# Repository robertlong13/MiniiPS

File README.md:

# MiniiPS
Custom regulator board for miniaturized Wii. Provides 1V, 1.15V, 3.3V, 5V. Similar to the PowerMiiLite, but larger and a few extra features specific to my personal project. Should be good for any wall-powered mini Wii project.

### Goals for this power supply
* Be small. Can't really afford much more space than 20mm by 60mm
* Use a 5V 3A USB-C charger for input power
* Have an enable pin for turning on and off the power supply. The slide switch I'm using for power is only rated for 200mA.
* Design the 3.3V, 1.15V, and 1V regulators for 3A output, and 15V input voltage. I'm over-engineering to give myself maximum chance of getting it right on the first try, instead of pushing all my components right to their spec. There could be some reason I this is a bad idea, but I can't think of one.
* Be easy to hand assemble (using skillet reflow) and rework. An automated assembly run is out of the question. Smallest passives are 0603 (1608 metric).

To power on the outputs, the enable pad must be pulled high with your power switch. By default, that pad is pulled low with a 10K resistor.

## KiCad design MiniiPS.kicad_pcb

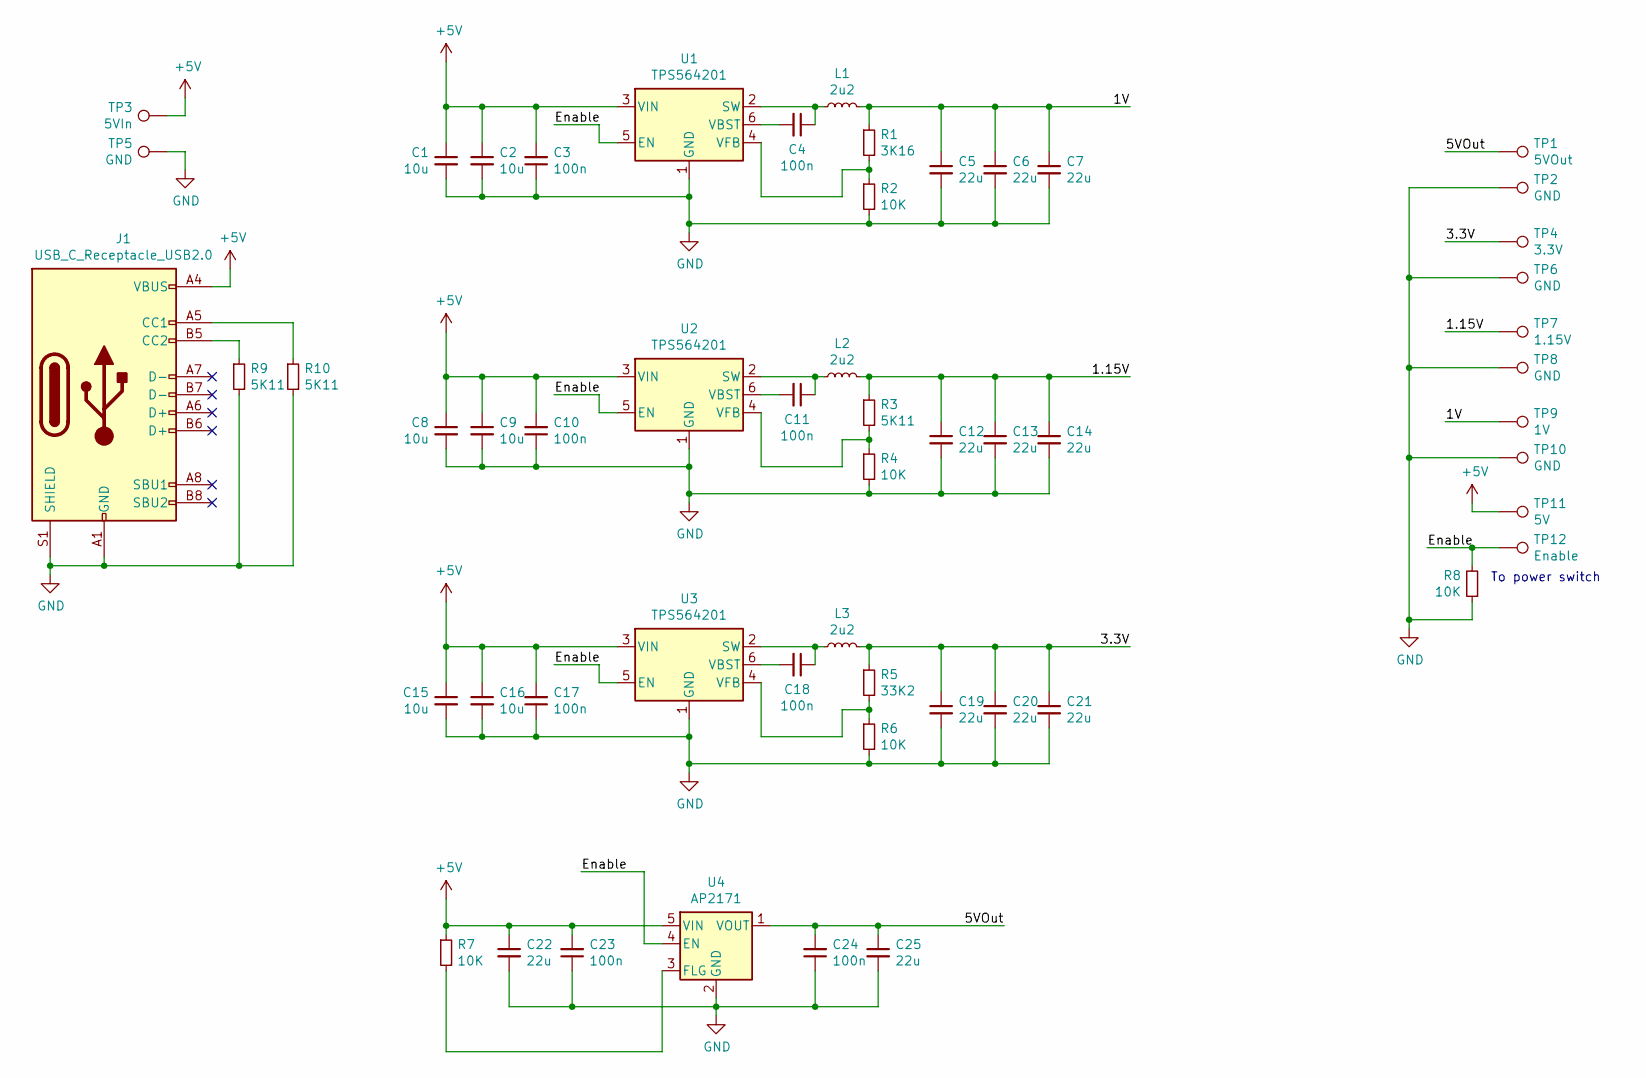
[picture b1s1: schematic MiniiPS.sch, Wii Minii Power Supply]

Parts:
C1, C2, C8, C9, C15, C16: 10u; C_0805_2012Metric; MFG Part Num TMK212BBJ106KG-T
C3, C4, C10, C11, C17, C18, C23, C24: 100n; C_0603_1608Metric; MFG Part Num CL10B104KB8NNNC
C5, C6, C7, C12, C13, C14, C19, C20, C21, C22, C25: 22u; C_0805_2012Metric; MFG Part Num CL21A226MQQNNNE
J1: USB_C_Receptacle_USB2.0; USB_C_Receptacle_GCT_USB4085; MFG Part Num USB4085-GF-A
L1, L2, L3: 2u2; MFG Part Num 1264EY-2R2N=P3
R1: 3K16; R_0603_1608Metric; MFG Part Num RMCF0603FT3K16
R2, R4, R6, R7, R8: 10K; R_0603_1608Metric; MFG Part Num RMCF0603FT10K0
R3, R9, R10: 5K11; R_0603_1608Metric; MFG Part Num RMCF0603FT5K11
R5: 33K2; R_0603_1608Metric; MFG Part Num RMCF0603FT33K2
TP1: 5VOut; TestPoint_Pad_4.0x4.0mm
TP2, TP5, TP6, TP8, TP10: GND; TestPoint_Pad_4.0x4.0mm
TP3: 5VIn; TestPoint_Pad_4.0x4.0mm
TP4: 3.3V; TestPoint_Pad_4.0x4.0mm
TP7: 1.15V; TestPoint_Pad_4.0x4.0mm
TP9: 1V; TestPoint_Pad_4.0x4.0mm
TP11: 5V; TestPoint_Pad_4.0x4.0mm
TP12: Enable; TestPoint_Pad_4.0x4.0mm
U1, U2, U3: TPS564201; SOT-23-6; MFG Part Num TPS564201DDCR
U4: AP2171; SOT-23-5; MFG Part Num AP2171WG-7

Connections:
+5V: C1.1, C2.1, C3.2, C8.1, C9.1, C10.2, C15.1, C16.1, C17.2, C22.1, C23.2, J1.A4 (VBUS), J1.A9 (VBUS), J1.B4 (VBUS), J1.B9 (VBUS), R7.1, TP3.1, TP11.1, U1.3 (VIN), U2.3 (VIN), U3.3 (VIN), U4.5 (VIN)
/1.15V: C12.1, C13.1, C14.1, L2.2, R3.1, TP7.1
/1V: C5.1, C6.1, C7.1, L1.2, R1.1, TP9.1
/3.3V: C19.1, C20.1, C21.1, L3.2, R5.1, TP4.1
/5VOut: C24.2, C25.1, TP1.1, U4.1 (VOUT)
/Enable: R8.2, TP12.1, U1.5 (EN), U2.5 (EN), U3.5 (EN), U4.4 (EN)
GND: C1.2, C2.2, C3.1, C5.2, C6.2, C7.2, C8.2, C9.2, C10.1, C12.2, C13.2, C14.2, C15.2, C16.2, C17.1, C19.2, C20.2, C21.2, C22.2, C23.1, C24.1, C25.2, J1.A1 (GND), J1.A12 (GND), J1.B1 (GND), J1.B12 (GND), J1.S1 (SHIELD), R2.2, R4.2, R6.2, R8.1, R9.2, R10.2, TP2.1, TP5.1, TP6.1, TP8.1, TP10.1, U1.1 (GND), U2.1 (GND), U3.1 (GND), U4.2 (GND)
unnamed: C4.1, L1.1, U1.2 (SW)
unnamed: C4.2, U1.6 (VBST)
unnamed: C11.1, L2.1, U2.2 (SW)
unnamed: C11.2, U2.6 (VBST)
unnamed: C18.1, L3.1, U3.2 (SW)
unnamed: C18.2, U3.6 (VBST)
unnamed: J1.A5 (CC1), R10.1
unnamed: J1.B5 (CC2), R9.1
unnamed: R1.2, R2.1, U1.4 (VFB)
unnamed: R3.2, R4.1, U2.4 (VFB)
unnamed: R5.2, R6.1, U3.4 (VFB)
unnamed: R7.2, U4.3 (FLG)

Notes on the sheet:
To power switch

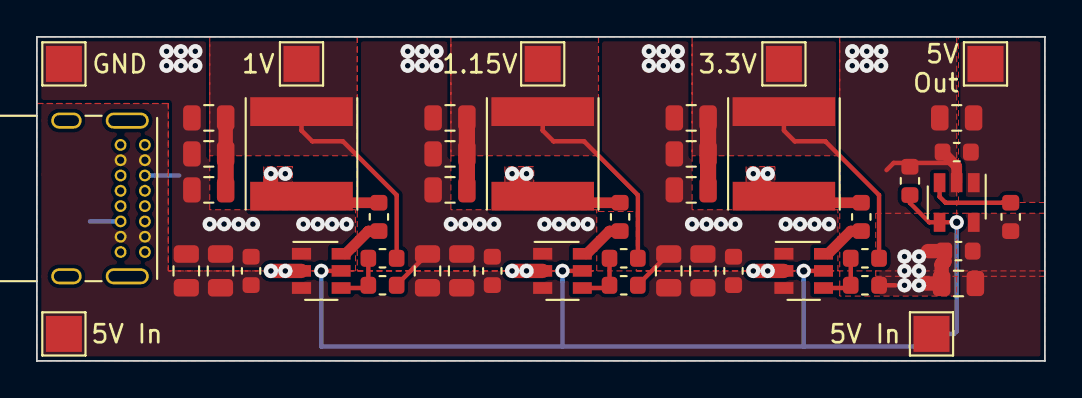
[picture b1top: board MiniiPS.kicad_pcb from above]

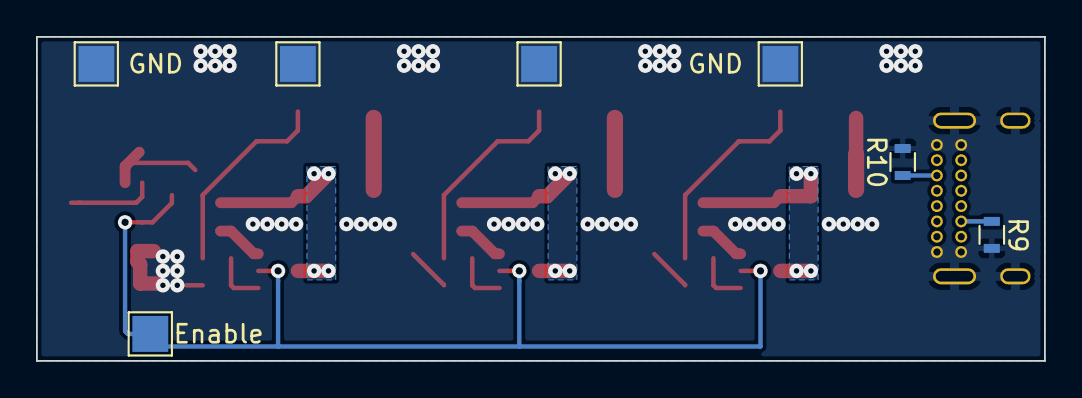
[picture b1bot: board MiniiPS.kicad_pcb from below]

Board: 2 copper layers, 56.0 x 18.0 mm, 55 parts (7 on the bottom side), 19 nets.

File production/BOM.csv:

Reference(s),Value,MFG Name,MFG Part Num,Description,Qty
"C1, C2, C8, C9, C15, C16",10u,Taiyo Yuden,TMK212BBJ106KG-T,CAP CER 10UF 25V X5R 0805,6
"C3, C4, C10, C11, C17, C18, C23, C24",100n,Samsung Electro-Mechanics,CL10B104KB8NNNC,CAP CER 0.1UF 50V X7R 0603,8
"C5, C6, C7, C12, C13, C14, C19, C20, C21, C22, C25",22u,Samsung Electro-Mechanics,CL21A226MQQNNNE,CAP CER 22UF 6.3V X5R 0805,11
J1,,GCT,USB4085-GF-A,CONN RCPT USB2.0 TYPEC 16POS,1
"L1, L2, L3",2u2,"	Murata Electronics",1264EY-2R2N=P3,FIXED IND 2.2UH 7.8A 19.2 MOHM,3
R1,3K16,Stackpole Electronics Inc,RMCF0603FT3K16,RES 3.16K OHM 1% 1/10W 0603,1
"R2, R4, R6, R7, R8",10K,Stackpole Electronics Inc,RMCF0603FT10K0,RES 10K OHM 1% 1/10W 0603,5
"R3, R9, R10",5K11,Stackpole Electronics Inc,RMCF0603FT5K11,RES 5.11K OHM 1% 1/10W 0603,3
R5,33K2,Stackpole Electronics Inc,RMCF0603FT33K2,RES 33.2K OHM 1% 1/10W 0603,1
"U1, U2, U3",TPS564201,Texas Instruments,TPS564201DDCR,IC REG BUCK ADJ 4A TSOT23-6,3
U4,AP2171,Diodes Incorporated,AP2171WG-7,"	IC PWR SWITCH P-CHAN 1:1 SOT25",1

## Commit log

2020-03-09 Add initial source files
